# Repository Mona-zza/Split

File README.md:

# Split Mechanical Keyboard

The keyboard uses a split layout with around 76 keys, The design is meant to be customizable and DIY-friendly. It uses Kailh hot-swap sockets, which means switches can be replaced anytime without needing to desolder them. This makes it easy to experiment with different switches later. For the controller, I used the nRF52840 development board, which works well with ZMK firmware. ZMK alows the keyboard to support Bluetooth, so it can be used wirelessly. It also support customizable keymaps, layers, and other advanced keyboard features. 

Designing the PCB took a lot more time than I expected. there were many small issues during routing and schematic checks. I spent quite a lot of time fixing different problems and improving the layout. After several iterations and debugging, the **PCB now finally passes both DRC (Design Rule Check) and ERC (Electrical Rule Check) with 0 errors**. Fixing all those issues took a lot of effort, but it was really satisfying to finally see everything clean in KiCad. The keyboard uses 76 mechanical switches, and each switch has a 1N4148 diode for the key matrix. Stabilizers are used for larger keys, and the switches are mounted using Kailh hot-swap sockets. Keycaps and switchs can be changed depending on personal preference. Also one of my fried recently built his own keyboard through stasis and he have some left over part which I can take use in when I'll built this keyboard, he even told me he'll be helping me to built this!!

One goal of this project was also to keep the build relatively affordable. Based on the current Bill of Materials, the estimated total cost is around ₹10,455 (~$110.72 USD) including PCB manufacturing and other components. I tried my best to keep it in budget, I tried to get maximum thing from one place (amazon) in budget to make things simple and save in shipping charges. Also I'll buy the PCBs locally and it would cost me around $20.

Overall, this project was mainly built for learning, experimenting, and having fun with hardware design. It was a really good experience going through the full PCB design process and understanding how keyboards work internally. If someone finds this project interesting or wants to build their own version of it, that would be really awesome.

## Cart:

## Bill of Materials (BOM) – Split Keyboard

| # | Component | Quantity | Unit Price | Total | Link |
|---|-----------|---------|-----------|------|------|
| 1 | Kailh Hot-Swap Sockets | 1 pack (~100 pcs) | ₹2476 | ₹2476 | https://www.amazon.in/gp/product/B0GHR248QJ) |
| 2 | Mechanical Switches | 76 (1 pack) | ₹1965 | ₹1965 | https://www.amazon.in/gp/product/B0F53HLG5M |
| 3 | Stabilizers | 1 pack | ₹1,929 | ₹1,929 | https://www.amazon.in/gp/product/B0CL195BK7 |
| 4 | Keycaps | 1 sets | ₹928 | ₹928 | https://www.amazon.in/gp/product/B0F3883M9C |
| 5 | 1N4148 Diodes | 1 pack (~100 pcs) | ₹285 | ₹285 | https://www.amazon.in/gp/product/B0FJLP12GX |
| 6 | nRF52840 Microcontroller | 1 | ₹758 | ₹758 | https://robu.in/product/promicro-nrf52840-development-board/ |
| 7 | PCB (Will buy it locally) | 1 order (2PCB) | $20 | ≈ ₹1838 | — |

---
### Total Estimated Cost

| Item | Cost |
|-----|------|
| Components Total | ₹8,567 |
| PCB | ≈ ₹1,888 |
| **Total Build Cost** | **≈ ₹10,455** (**$110.72 USD**) |

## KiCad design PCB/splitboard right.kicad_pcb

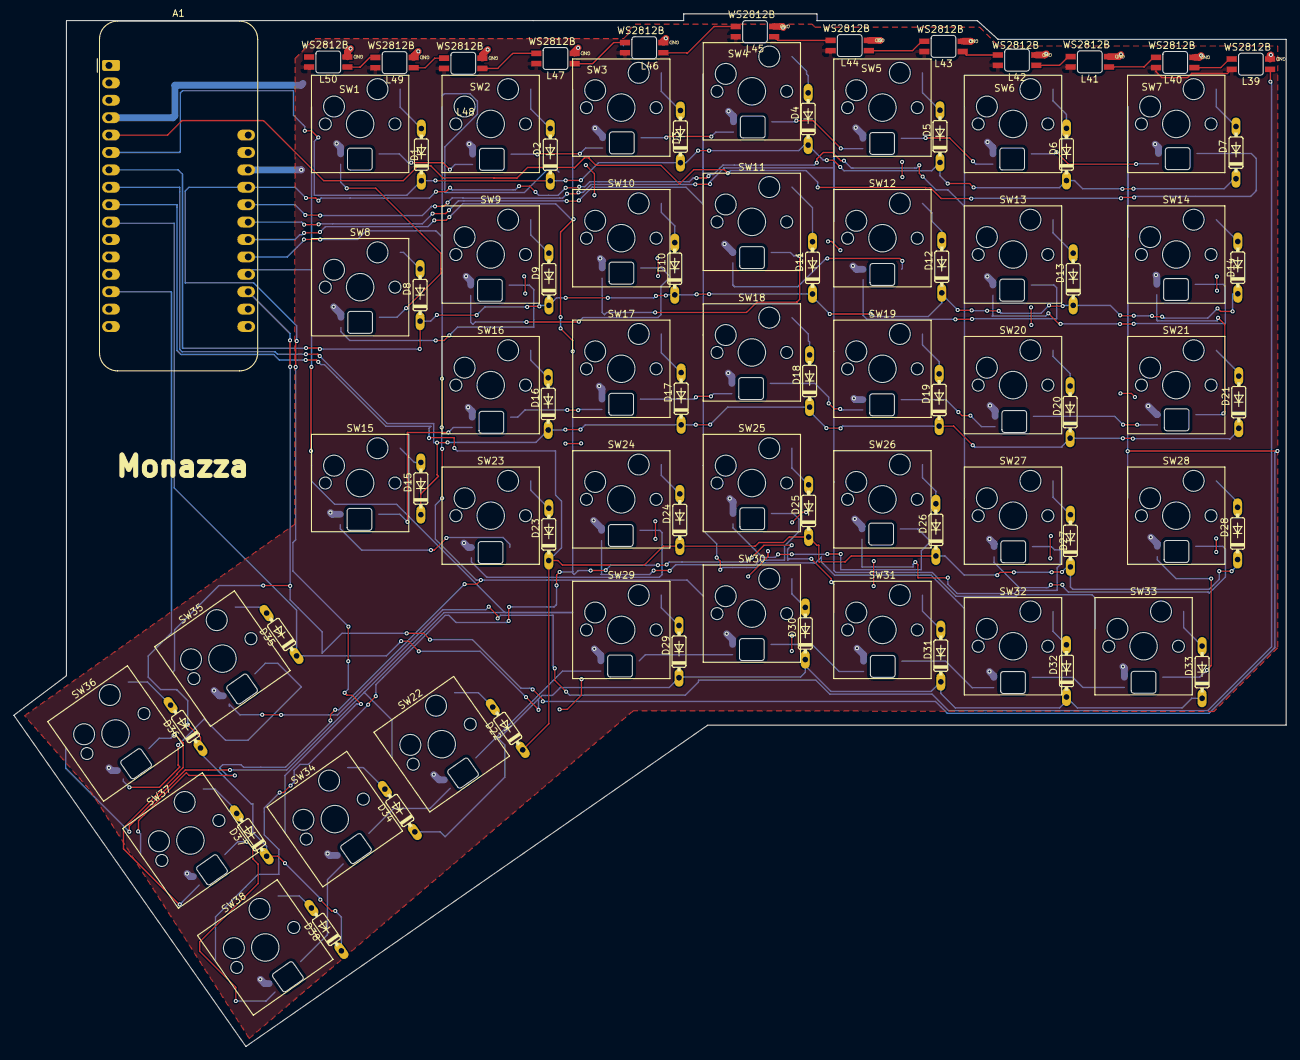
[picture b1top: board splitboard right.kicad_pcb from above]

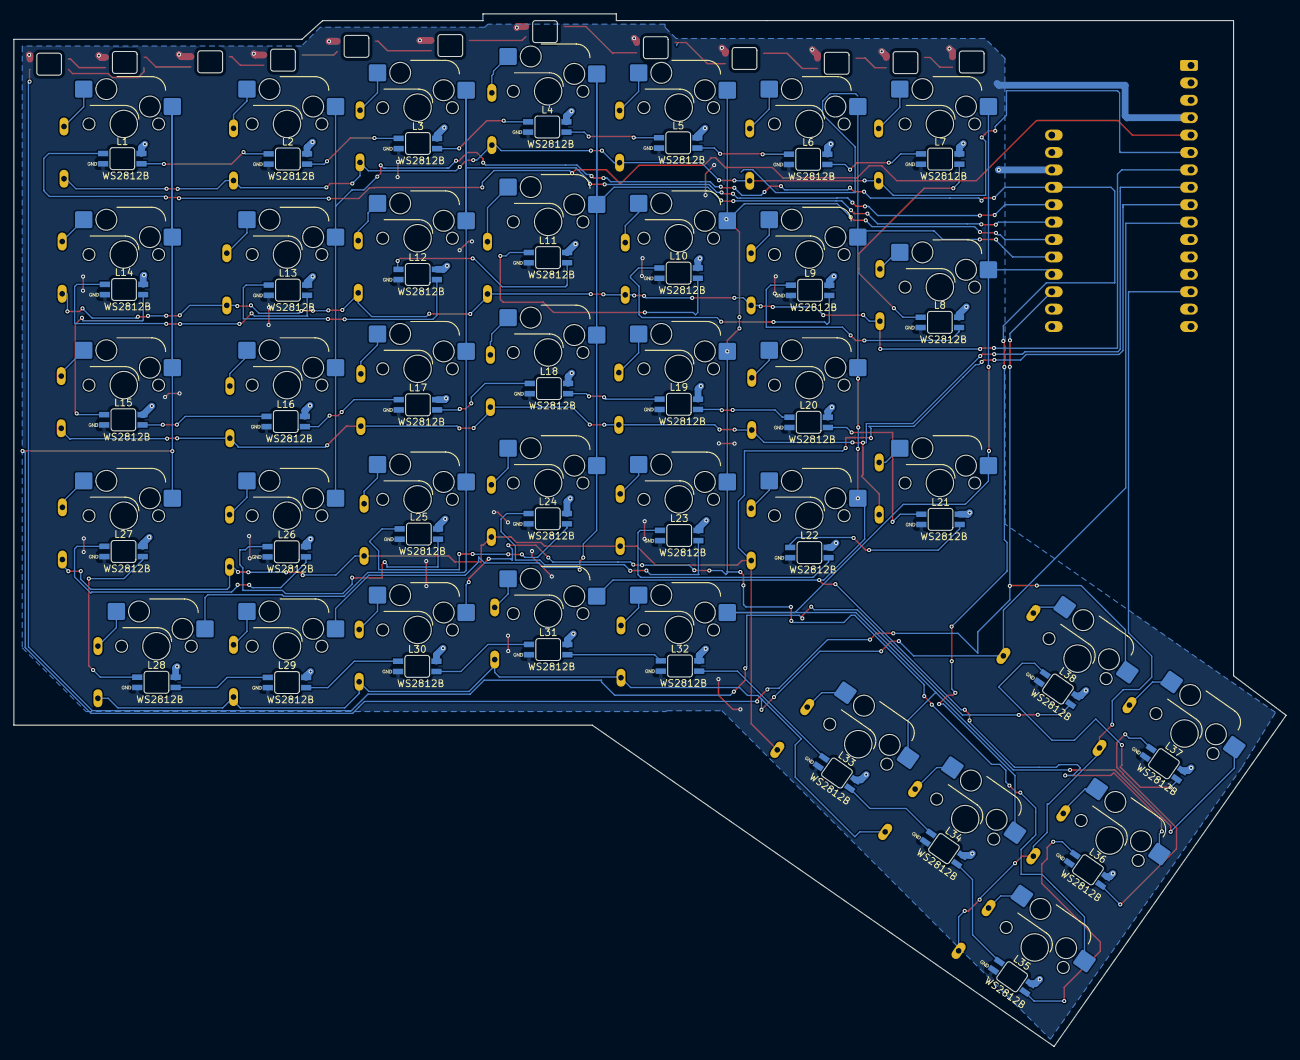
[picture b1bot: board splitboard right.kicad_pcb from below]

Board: 2 copper layers, 185.6 x 150.6 mm, 127 parts (38 on the bottom side), 103 nets.

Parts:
A1: Adafruit_Feather_Generic; Adafruit_Feather
D1, D2, D3, D4, D5, D6, D7, D8, D9, D10, D11, D12, D13, D14, D15, D16, D17, D18, D19, D20, D21, D22, D23, D24, D25, D26, D27, D28, D29, D30, D31, D32, D33, D34, D35, D36, D37, D38: D_45deg; DO35-7
L1, L2, L3, L4, L5, L6, L7, L8, L9, L10, L11, L12, L13, L14, L15, L16, L17, L18, L19, L20, L21, L22, L23, L24, L25, L26, L27, L28, L29, L30, L31, L32, L33, L34, L35, L36, L37, L38, L39, L40, L41, L42, L43, L44, L45, L46, L47, L48, L49, L50: WS2812B; BAcklight
SW1, SW2, SW3, SW4, SW5, SW6, SW9, SW10, SW11, SW12, SW13, SW16, SW17, SW18, SW19, SW20, SW23, SW24, SW25, SW26, SW27, SW29, SW30, SW31, SW32, SW33, SW35, SW36, SW37, SW38: SW_Push; SW_Hotswap_Kailh_MX_1.00u
SW7, SW14, SW21, SW28: SW_Push; SW_Hotswap_Kailh_MX_1.50u
SW8, SW15: SW_Push; SW_Hotswap_Kailh_MX_1.50u_90deg
SW22, SW34: SW_Push; SW_Hotswap_Kailh_MX_2.00u_90deg

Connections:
+5V: A1.26 (USB), L1.1 (VDD), L2.1 (VDD), L3.1 (VDD), L4.1 (VDD), L5.1 (VDD), L6.1 (VDD), L7.1 (VDD), L8.1 (VDD), L9.1 (VDD), L10.1 (VDD), L11.1 (VDD), L12.1 (VDD), L13.1 (VDD), L14.1 (VDD), L15.1 (VDD), L16.1 (VDD), L17.1 (VDD), L18.1 (VDD), L19.1 (VDD), L20.1 (VDD), L21.1 (VDD), L22.1 (VDD), L23.1 (VDD), L24.1 (VDD), L25.1 (VDD), L26.1 (VDD), L27.1 (VDD), L28.1 (VDD), L29.1 (VDD), L30.1 (VDD), L31.1 (VDD), L32.1 (VDD), L33.1 (VDD), L34.1 (VDD), L35.1 (VDD), L36.1 (VDD), L37.1 (VDD), L38.1 (VDD), L39.1 (VDD), L40.1 (VDD), L41.1 (VDD), L42.1 (VDD), L43.1 (VDD), L44.1 (VDD), L45.1 (VDD), L46.1 (VDD), L47.1 (VDD), L48.1 (VDD), L49.1 (VDD), L50.1 (VDD)
COL1: A1.20 (D1), SW1.1, SW8.1, SW15.1, SW22.1, SW29.1, SW36.1
COL2: A1.21 (D2), SW2.1, SW9.1, SW16.1, SW23.1, SW30.1, SW37.1
COL3: A1.22 (D3), SW3.1, SW10.1, SW17.1, SW24.1, SW31.1, SW38.1
COL4: A1.23 (D4), SW4.1, SW11.1, SW18.1, SW25.1, SW32.1
COL5: A1.24 (D5), SW5.1, SW12.1, SW19.1, SW26.1, SW33.1
COL6: A1.25 (D6), SW6.1, SW13.1, SW20.1, SW27.1, SW34.1
COL7: A1.19 (D0), SW7.1, SW14.1, SW21.1, SW28.1, SW35.1
GND: A1.4 (GND), L1.3 (VSS), L2.3 (VSS), L3.3 (VSS), L4.3 (VSS), L5.3 (VSS), L6.3 (VSS), L7.3 (VSS), L8.3 (VSS), L9.3 (VSS), L10.3 (VSS), L11.3 (VSS), L12.3 (VSS), L13.3 (VSS), L14.3 (VSS), L15.3 (VSS), L16.3 (VSS), L17.3 (VSS), L18.3 (VSS), L19.3 (VSS), L20.3 (VSS), L21.3 (VSS), L22.3 (VSS), L23.3 (VSS), L24.3 (VSS), L25.3 (VSS), L26.3 (VSS), L27.3 (VSS), L28.3 (VSS), L29.3 (VSS), L30.3 (VSS), L31.3 (VSS), L32.3 (VSS), L33.3 (VSS), L34.3 (VSS), L35.3 (VSS), L36.3 (VSS), L37.3 (VSS), L38.3 (VSS), L39.3 (VSS), L40.3 (VSS), L41.3 (VSS), L42.3 (VSS), L43.3 (VSS), L44.3 (VSS), L45.3 (VSS), L46.3 (VSS), L47.3 (VSS), L48.3 (VSS), L49.3 (VSS), L50.3 (VSS)
unnamed: D1.2 (A), SW1.2
unnamed: D2.2 (A), SW2.2
unnamed: D3.2 (A), SW3.2
unnamed: D4.2 (A), SW4.2
unnamed: D5.2 (A), SW5.2
unnamed: D6.2 (A), SW6.2
unnamed: D7.2 (A), SW7.2
unnamed: D8.2 (A), SW8.2
unnamed: D9.2 (A), SW9.2
unnamed: D10.2 (A), SW10.2
unnamed: D11.2 (A), SW11.2
unnamed: D12.2 (A), SW12.2
unnamed: D13.2 (A), SW13.2
unnamed: D14.2 (A), SW14.2
unnamed: D15.2 (A), SW15.2
unnamed: D16.2 (A), SW16.2
unnamed: D17.2 (A), SW17.2
unnamed: D18.2 (A), SW18.2
unnamed: D19.2 (A), SW19.2
unnamed: D20.2 (A), SW20.2
unnamed: D21.2 (A), SW21.2
unnamed: D22.2 (A), SW22.2
unnamed: D23.2 (A), SW23.2
unnamed: D24.2 (A), SW24.2
unnamed: D25.2 (A), SW25.2
unnamed: D26.2 (A), SW26.2
unnamed: D27.2 (A), SW27.2
unnamed: D28.2 (A), SW28.2
unnamed: D29.2 (A), SW29.2
unnamed: D30.2 (A), SW30.2
unnamed: D31.2 (A), SW31.2
unnamed: D32.2 (A), SW32.2
unnamed: D33.2 (A), SW33.2
unnamed: D34.2 (A), SW34.2
unnamed: D35.2 (A), SW35.2
unnamed: D36.2 (A), SW36.2
unnamed: D37.2 (A), SW37.2
unnamed: D38.2 (A), SW38.2
unnamed: L1.2 (DOUT), L2.4 (DIN)
unnamed: L2.2 (DOUT), L3.4 (DIN)
unnamed: L3.2 (DOUT), L4.4 (DIN)
unnamed: L4.2 (DOUT), L5.4 (DIN)
unnamed: L5.2 (DOUT), L6.4 (DIN)
unnamed: L6.2 (DOUT), L7.4 (DIN)
unnamed: L7.2 (DOUT), L8.4 (DIN)
unnamed: L8.2 (DOUT), L9.4 (DIN)
unnamed: L9.2 (DOUT), L10.4 (DIN)
unnamed: L10.2 (DOUT), L11.4 (DIN)
unnamed: L11.2 (DOUT), L12.4 (DIN)
unnamed: L12.2 (DOUT), L13.4 (DIN)
unnamed: L13.2 (DOUT), L14.4 (DIN)
unnamed: L14.2 (DOUT), L15.4 (DIN)
unnamed: L15.2 (DOUT), L16.4 (DIN)
unnamed: L16.2 (DOUT), L17.4 (DIN)
unnamed: L17.2 (DOUT), L18.4 (DIN)
unnamed: L18.2 (DOUT), L19.4 (DIN)
unnamed: L19.2 (DOUT), L20.4 (DIN)
unnamed: L20.2 (DOUT), L21.4 (DIN)
unnamed: L21.2 (DOUT), L22.4 (DIN)
unnamed: L22.2 (DOUT), L23.4 (DIN)
unnamed: L23.2 (DOUT), L24.4 (DIN)
unnamed: L24.2 (DOUT), L25.4 (DIN)
unnamed: L25.2 (DOUT), L26.4 (DIN)
unnamed: L26.2 (DOUT), L27.4 (DIN)
unnamed: L27.2 (DOUT), L28.4 (DIN)
unnamed: L28.2 (DOUT), L29.4 (DIN)
unnamed: L29.2 (DOUT), L30.4 (DIN)
unnamed: L30.2 (DOUT), L31.4 (DIN)
unnamed: L31.2 (DOUT), L32.4 (DIN)
unnamed: L32.2 (DOUT), L33.4 (DIN)
unnamed: L33.2 (DOUT), L34.4 (DIN)
unnamed: L34.2 (DOUT), L35.4 (DIN)
unnamed: L35.2 (DOUT), L36.4 (DIN)
unnamed: L36.2 (DOUT), L37.4 (DIN)
unnamed: L37.2 (DOUT), L38.4 (DIN)
unnamed: L38.2 (DOUT), L39.4 (DIN)
unnamed: L39.2 (DOUT), L40.4 (DIN)
unnamed: L40.2 (DOUT), L41.4 (DIN)
unnamed: L41.2 (DOUT), L42.4 (DIN)
unnamed: L42.2 (DOUT), L43.4 (DIN)
unnamed: L43.2 (DOUT), L44.4 (DIN)
unnamed: L44.2 (DOUT), L45.4 (DIN)
unnamed: L45.2 (DOUT), L46.4 (DIN)
unnamed: L46.2 (DOUT), L47.4 (DIN)
unnamed: L47.2 (DOUT), L48.4 (DIN)
unnamed: L48.2 (DOUT), L49.4 (DIN)
unnamed: L49.2 (DOUT), L50.4 (DIN)
RGB: A1.5 (A0), L1.4 (DIN)
ROW1: A1.6 (A1), D1.1 (K), D2.1 (K), D3.1 (K), D4.1 (K), D5.1 (K), D6.1 (K), D7.1 (K)
ROW2: A1.7 (A2), D8.1 (K), D9.1 (K), D10.1 (K), D11.1 (K), D12.1 (K), D13.1 (K), D14.1 (K)
ROW3: A1.8 (A3), D15.1 (K), D16.1 (K), D17.1 (K), D18.1 (K), D19.1 (K), D20.1 (K), D21.1 (K)
ROW4: A1.9 (A4), D22.1 (K), D23.1 (K), D24.1 (K), D25.1 (K), D26.1 (K), D27.1 (K), D28.1 (K)
ROW5: A1.10 (A5), D29.1 (K), D30.1 (K), D31.1 (K), D32.1 (K), D33.1 (K), D34.1 (K), D35.1 (K)
ROW6: A1.14 (RX), D36.1 (K), D37.1 (K), D38.1 (K)

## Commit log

2026-05-10 Add README for split mechanical keyboard project
    Added detailed project description, images, and Bill of Materials for the split mechanical keyboard.
